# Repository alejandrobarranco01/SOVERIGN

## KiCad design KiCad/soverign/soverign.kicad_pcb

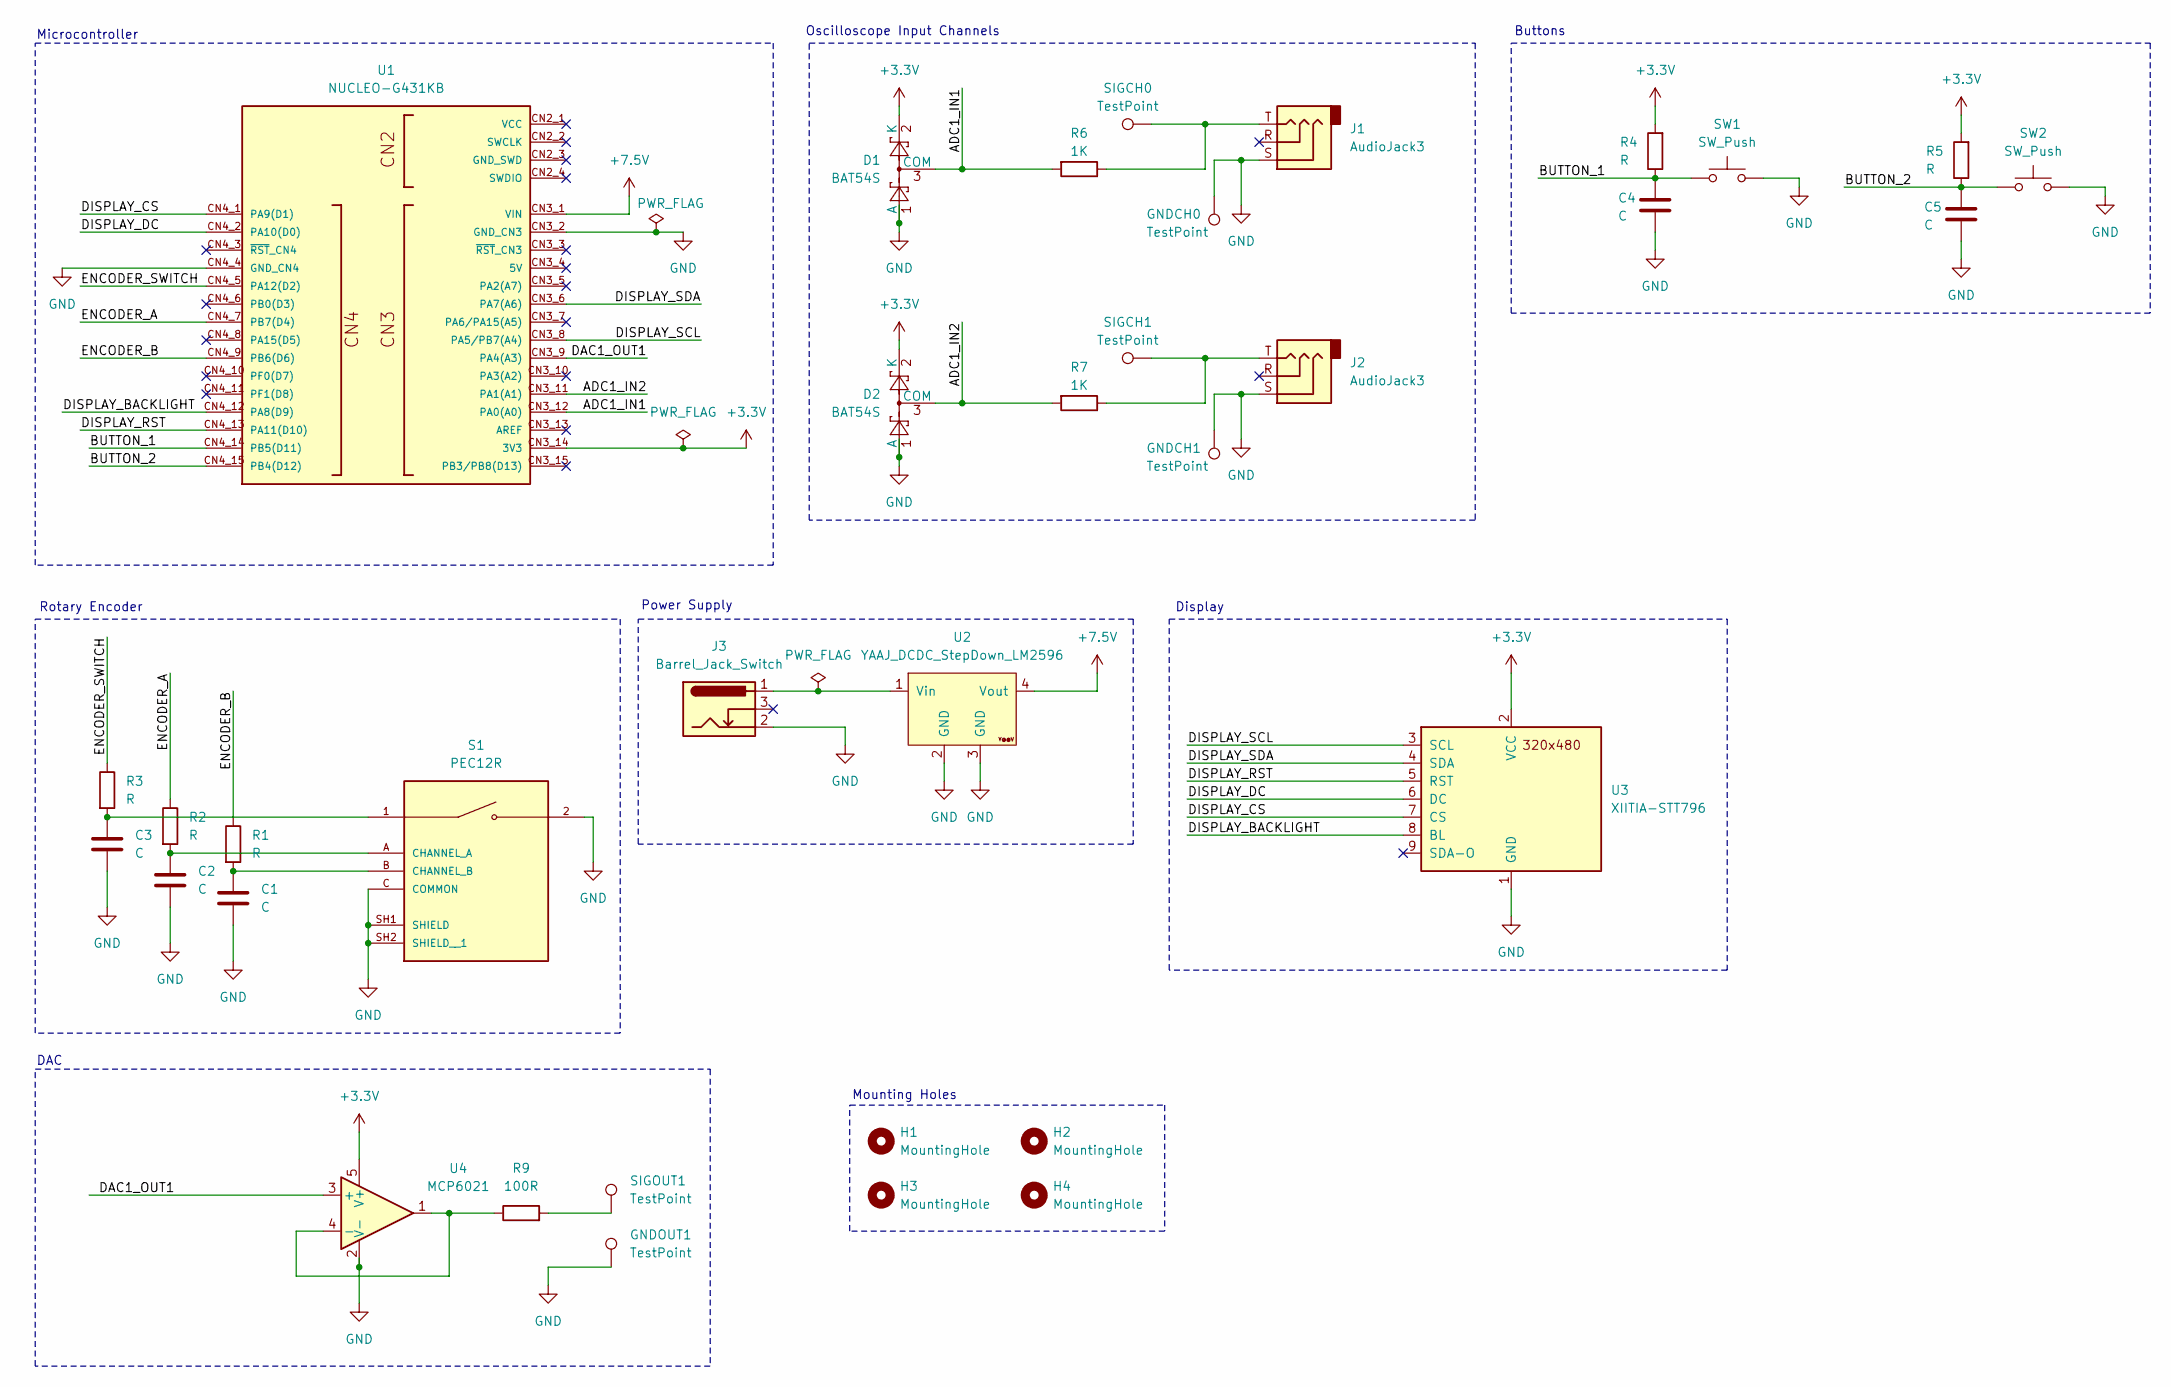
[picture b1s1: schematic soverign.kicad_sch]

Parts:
C1, C2, C3, C4, C5: C; C_Disc_D5.0mm_W2.5mm_P5.00mm
D1, D2: BAT54S; SOT-23
GNDCH0, GNDCH1: TestPoint; PinHeader_1x01_P2.54mm_Vertical
GNDOUT1: TestPoint; PinHeader_1x01_P2.54mm_Vertical
H1, H2, H3, H4: MountingHole; MountingHole_2.2mm_M2_DIN965_Pad
J1, J2: AudioJack3; Jack_3.5mm_CUI_SJ1-3523N_Horizontal
J3: Barrel_Jack_Switch; BarrelJack_Horizontal
R1, R2, R3, R4, R5: R; R_Axial_DIN0207_L6.3mm_D2.5mm_P10.16mm_Horizontal
R6, R7: 1K; R_Axial_DIN0207_L6.3mm_D2.5mm_P10.16mm_Horizontal
R9: 100R; R_Axial_DIN0207_L6.3mm_D2.5mm_P10.16mm_Horizontal
S1: PEC12R; PARTREV 07/21
SIGCH0, SIGCH1: TestPoint; PinHeader_1x01_P2.54mm_Vertical
SIGOUT1: TestPoint; PinHeader_1x01_P2.54mm_Vertical
SW1, SW2: SW_Push; SW_PUSH-12mm
U1: NUCLEO-G431KB; MODULE_NUCLEO-G431KB; PARTREV 2
U2: YAAJ_DCDC_StepDown_LM2596; LM2596
U3: XIITIA-STT796; XIITIA-ST7796
U4: MCP6021

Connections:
+3.3V: D1.2 (K), D2.2 (K), R4.2, R5.2, U1.CN3_14 (3V3), U3.2 (VCC), U4.5 (V+)
+7.5V: U1.CN3_1 (VIN), U2.4 (Vout)
/ADC1_IN1: D1.3 (COM), R6.2, U1.CN3_12 (PA0(A0))
/ADC1_IN2: D2.3 (COM), R7.2, U1.CN3_11 (PA1(A1))
/BUTTON_1: C4.1, R4.1, SW1.1, U1.CN4_14 (PB5(D11))
/BUTTON_2: C5.1, R5.1, SW2.1, U1.CN4_15 (PB4(D12))
/DAC1_OUT1: U1.CN3_9 (PA4(A3)), U4.3 (+)
/DISPLAY_BACKLIGHT: U1.CN4_12 (PA8(D9)), U3.8 (BL)
/DISPLAY_CS: U1.CN4_1 (PA9(D1)), U3.7 (CS)
/DISPLAY_DC: U1.CN4_2 (PA10(D0)), U3.6 (DC)
/DISPLAY_RST: U1.CN4_13 (PA11(D10)), U3.5 (RST)
/DISPLAY_SCL: U1.CN3_8 (PA5/PB7(A4)), U3.3 (SCL)
/DISPLAY_SDA: U1.CN3_6 (PA7(A6)), U3.4 (SDA)
/ENCODER_A: R2.1, U1.CN4_7 (PB7(D4))
/ENCODER_B: R1.1, U1.CN4_9 (PB6(D6))
/ENCODER_SWITCH: R3.1, U1.CN4_5 (PA12(D2))
GND: C1.2, C2.2, C3.2, C4.2, C5.2, D1.1 (A), D2.1 (A), GNDCH0.1, GNDCH1.1, GNDOUT1.1, J1.S, J2.S, J3.2, S1.2, S1.C (COMMON), S1.SH1 (SHIELD), S1.SH2 (SHIELD__1), SW1.2, SW2.2, U1.CN3_2 (GND_CN3), U1.CN4_4 (GND_CN4), U2.2 (GND), U2.3 (GND), U3.1 (GND), U4.2 (V-)
unnamed: C3.1, R3.2, S1.1
unnamed: J1.T, R6.1, SIGCH0.1
unnamed: J2.T, R7.1, SIGCH1.1
unnamed: R9.2, SIGOUT1.1
unnamed: C2.1, R2.2, S1.A (CHANNEL_A)
unnamed: C1.1, R1.2, S1.B (CHANNEL_B)
unnamed: J3.1, U2.1 (Vin)
unnamed: R9.1, U4.1, U4.4 (-)

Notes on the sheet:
Oscilloscope Input Channels
Microcontroller
Rotary Encoder
Mounting Holes
Power Supply
Buttons
DAC
Display

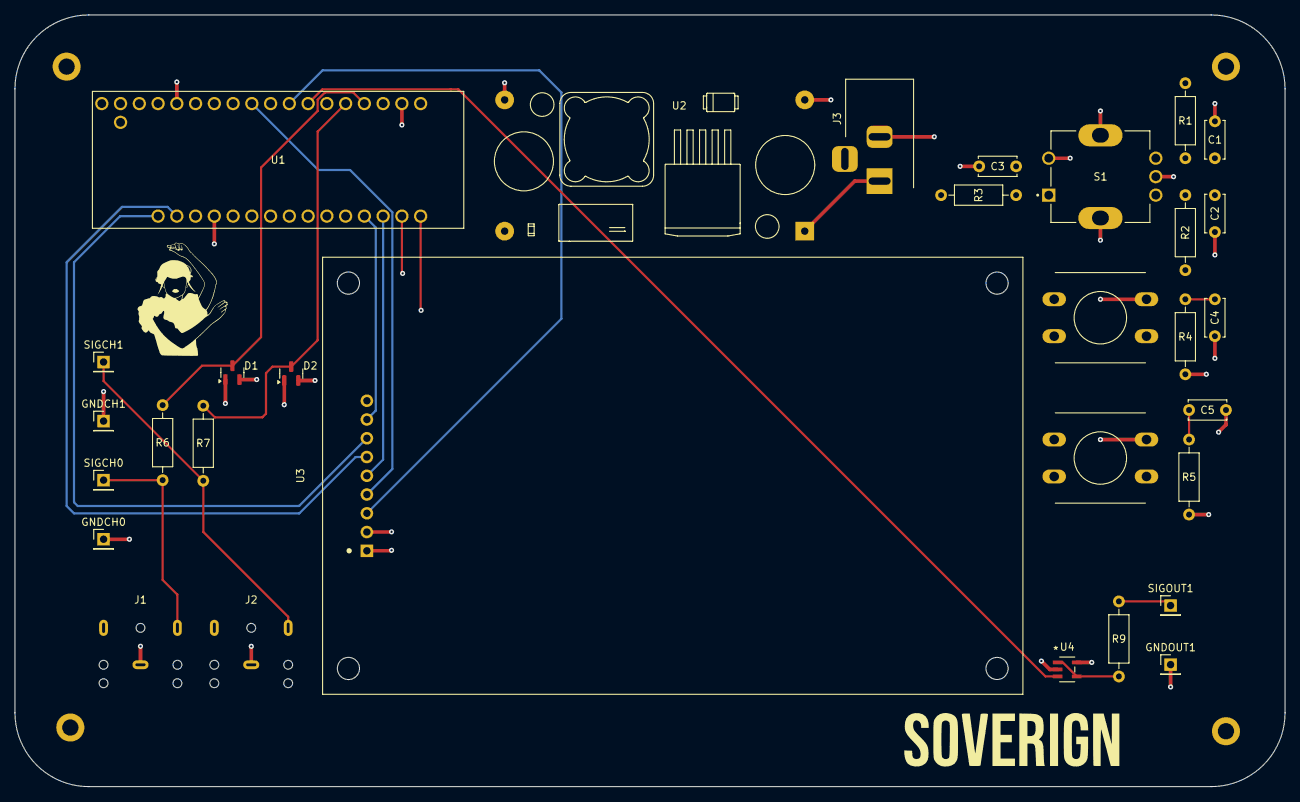
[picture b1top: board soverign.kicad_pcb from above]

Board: 4 copper layers, 172.0 x 104.5 mm, 35 parts (0 on the bottom side), 25 nets.

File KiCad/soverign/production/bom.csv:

Designator,Footprint,Quantity,Value,LCSC Part #
"C1, C2, C3, C4, C5",C_Disc_D5.0mm_W2.5mm_P5.00mm,5,C,
"D1, D2",SOT-23,2,BAT54S,
"GNDCH0, GNDCH1, GNDOUT1, SIGCH0, SIGCH1, SIGOUT1",PinHeader_1x01_P2.54mm_Vertical,6,TestPoint,
"J1, J2",Jack_3.5mm_CUI_SJ1-3523N_Horizontal,2,AudioJack3,
J3,BarrelJack_Horizontal,1,Barrel_Jack_Switch,
"R1, R2, R3, R4, R5",R_Axial_DIN0207_L6.3mm_D2.5mm_P10.16mm_Horizontal,5,R,
"R6, R7",R_Axial_DIN0207_L6.3mm_D2.5mm_P10.16mm_Horizontal,2,1K,
R9,R_Axial_DIN0207_L6.3mm_D2.5mm_P10.16mm_Horizontal,1,100R,
S1,PEC12R,1,PEC12R,
"SW1, SW2",SW_PUSH-12mm,2,SW_Push,
U1,MODULE_NUCLEO-G431KB,1,NUCLEO-G431KB,
U2,LM2596,1,YAAJ_DCDC_StepDown_LM2596,
U3,XIITIA-ST7796,1,XIITIA-STT796,
U4,MCP6021,1,MCP6021,

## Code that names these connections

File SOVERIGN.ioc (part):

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Mcu.Name=STM32G431K(6-8-B)Tx
Mcu.Package=LQFP32
Mcu.UserName=STM32G431KBTx
PA0.Mode=IN1-Single-Ended
PA0.Signal=ADC1_IN1
PA1.Mode=IN2-Single-Ended
PA1.Signal=ADC1_IN2
PA10.GPIOParameters=GPIO_Label
PA10.GPIO_Label=DISPLAY_DC
PA10.Signal=GPIO_Output
PA11.GPIOParameters=GPIO_Label
PA11.GPIO_Label=DISPLAY_RST
PA11.Signal=GPIO_Output
PA12.GPIOParameters=GPIO_Label
PA12.GPIO_Label=ENCODER_SWITCH
PA12.Signal=GPIO_Input
PA13.GPIOParameters=GPIO_Label
PA13.GPIO_Label=T_SWDIO
PA13.Signal=SYS_JTMS-SWDIO
PA14.GPIOParameters=GPIO_Label
PA14.GPIO_Label=T_SWCLK
PA14.Signal=SYS_JTCK-SWCLK
PA2.GPIOParameters=GPIO_Label
PA2.GPIO_Label=USART2_TX [ST-LINKV3E_VCP_RX]
PA2.Mode=Asynchronous
PA2.Signal=USART2_TX
PA3.GPIOParameters=GPIO_Label
PA3.GPIO_Label=USART2_RX [ST-LINKV3E_VCP_TX]
PA3.Mode=Asynchronous
PA3.Signal=USART2_RX
PA4.Signal=COMP_DAC11_group
PA5.Mode=Full_Duplex_Master
PA5.Signal=SPI1_SCK
PA6.Mode=Full_Duplex_Master
PA6.Signal=SPI1_MISO
PA7.Mode=Full_Duplex_Master
PA7.Signal=SPI1_MOSI
PA8.GPIOParameters=GPIO_Label
PA8.GPIO_Label=DISPLAY_BACKLIGHT
PA8.Signal=S_TIM1_CH1
PA9.GPIOParameters=GPIO_Label
PA9.GPIO_Label=DISPLAY_CS
PA9.Signal=GPIO_Output
PB3.GPIOParameters=GPIO_Label
PB3.GPIO_Label=T_SWO
PB3.Signal=SYS_JTDO-SWO
PB4.GPIOParameters=GPIO_PuPd,GPIO_Label,GPIO_ModeDefaultEXTI
PB4.GPIO_Label=BUTTON_2
PB4.GPIO_ModeDefaultEXTI=GPIO_MODE_IT_FALLING
PB4.GPIO_PuPd=GPIO_PULLUP
PB4.Signal=GPXTI4
PB5.GPIOParameters=GPIO_PuPd,GPIO_Label,GPIO_ModeDefaultEXTI
PB5.GPIO_Label=BUTTON_1
PB5.GPIO_ModeDefaultEXTI=GPIO_MODE_IT_FALLING
PB5.GPIO_PuPd=GPIO_PULLUP
PB5.Signal=GPXTI5
PB6.GPIOParameters=GPIO_Label
PB6.GPIO_Label=ENCODER_B
PB6.Signal=GPIO_Input
PB7.GPIOParameters=GPIO_Label
PB7.GPIO_Label=ENCODER_A
PB7.Signal=GPIO_Input
RCC.HSE_VALUE=8000000
RCC.SYSCLKFreq_VALUE=170000000
RCC.SYSCLKSource=RCC_SYSCLKSOURCE_PLLCLK
board=NUCLEO-G431KB
boardIOC=true

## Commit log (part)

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2026-05-13 Added basic circuitry for TCAN332G transceiver
